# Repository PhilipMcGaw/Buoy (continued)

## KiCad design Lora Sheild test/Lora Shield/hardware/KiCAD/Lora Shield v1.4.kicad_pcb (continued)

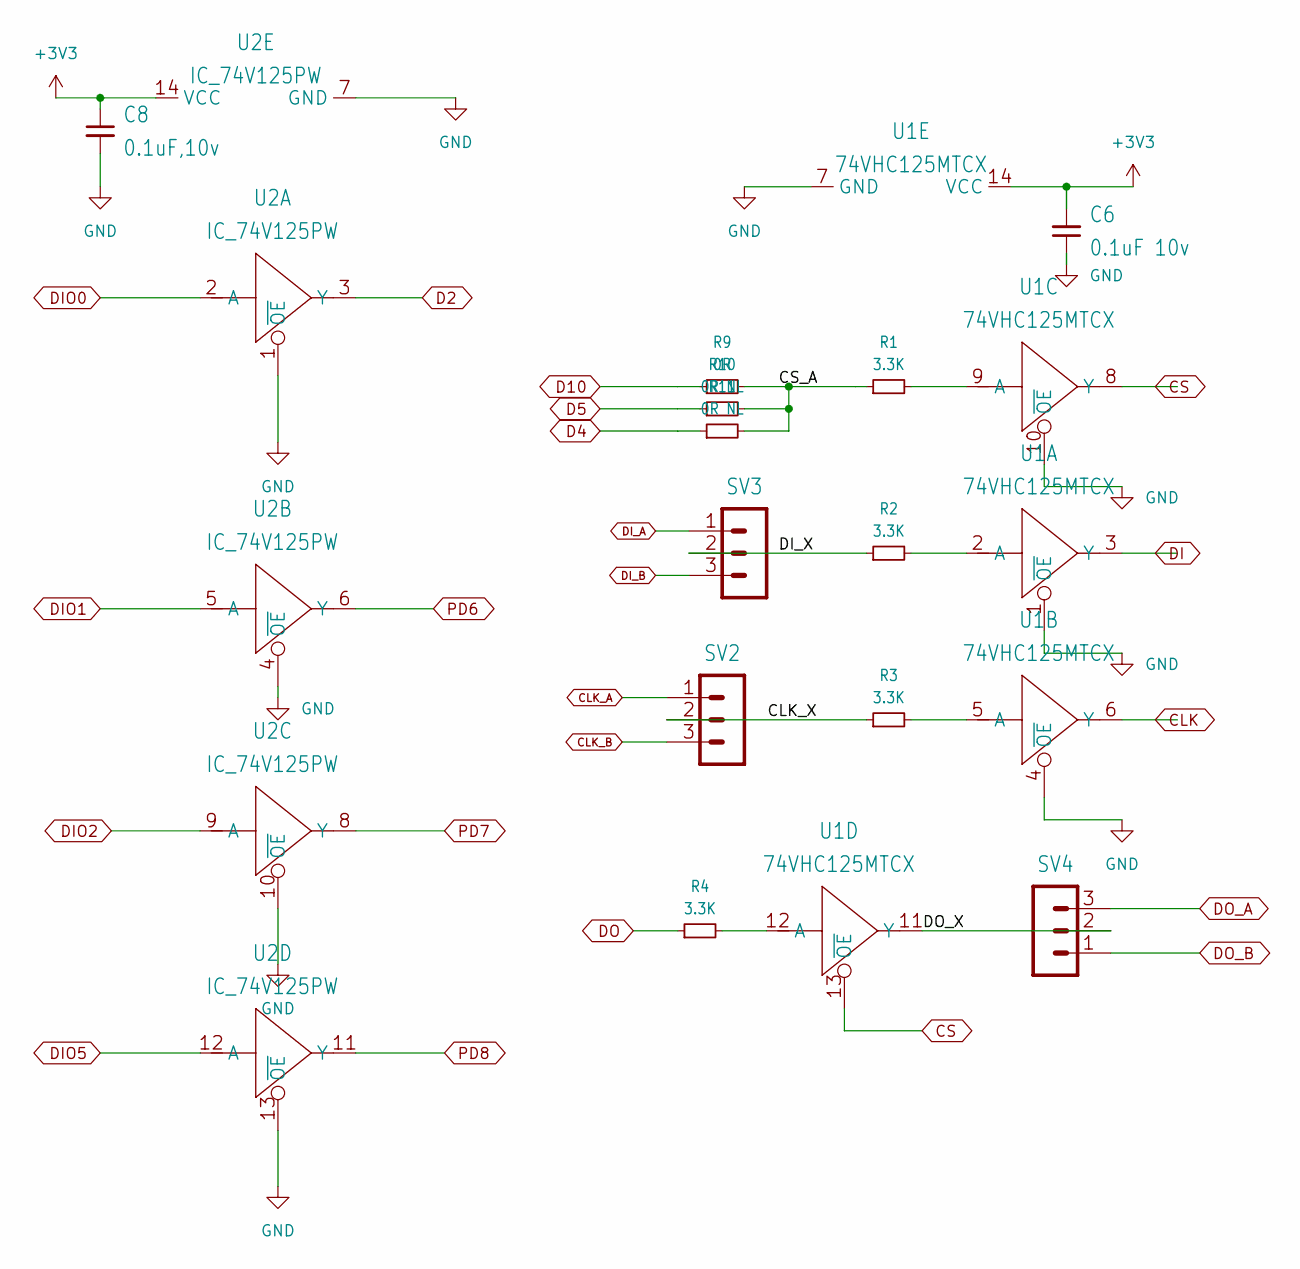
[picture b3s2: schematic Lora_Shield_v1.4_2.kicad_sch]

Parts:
C6: 0.1uF 10v; C0805
C8: 0.1uF,10v; C0805
R1, R2, R3, R4: 3.3K; R0603
R9: 0R; R0603
R10, R11: 0R NL; R0603
SV2, SV3, SV4: MA03-1
U1: 74VHC125MTCX; TSSOP14
U2: IC_74V125PW; IC_TSSOP14

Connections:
3V3: C6.2, C8.1, U1.14 (VCC), U2.14 (VCC); also elsewhere on the board
CLK: U1.6 (Y); also elsewhere on the board
CLK_A: SV2.1; also elsewhere on the board
CLK_B: SV2.3; also elsewhere on the board
CLK_X: R3.1, SV2.2
CS: U1.8 (Y), U1.13 (~OE); also elsewhere on the board
CS_A: R1.1, R9.2, R10.2, R11.2
D2: U2.3 (Y); also elsewhere on the board
D4: R11.1; also elsewhere on the board
D5: R10.1; also elsewhere on the board
D10: R9.1; also elsewhere on the board
DI: U1.3 (Y); also elsewhere on the board
DIO0: U2.2 (A); also elsewhere on the board
DIO1: U2.5 (A); also elsewhere on the board
DIO2: U2.9 (A); also elsewhere on the board
DIO5: U2.12 (A); also elsewhere on the board
DI_A: SV3.1; also elsewhere on the board
DI_B: SV3.3; also elsewhere on the board
DI_X: R2.1, SV3.2
DO: R4.1; also elsewhere on the board
DO_A: SV4.3; also elsewhere on the board
DO_B: SV4.1; also elsewhere on the board
DO_X: SV4.2, U1.11 (Y)
GND: C6.1, C8.2, U1.1 (~OE), U1.4 (~OE), U1.7 (GND), U1.10 (~OE), U2.1 (~OE), U2.4 (~OE), U2.7 (GND), U2.10 (~OE), U2.13 (~OE); also elsewhere on the board
unnamed: R4.2, U1.12 (A)
unnamed: R3.2, U1.5 (A)
unnamed: R2.2, U1.2 (A)
unnamed: R1.2, U1.9 (A)
PD6: U2.6 (Y); also elsewhere on the board
PD7: U2.8 (Y); also elsewhere on the board
PD8: U2.11 (Y); also elsewhere on the board

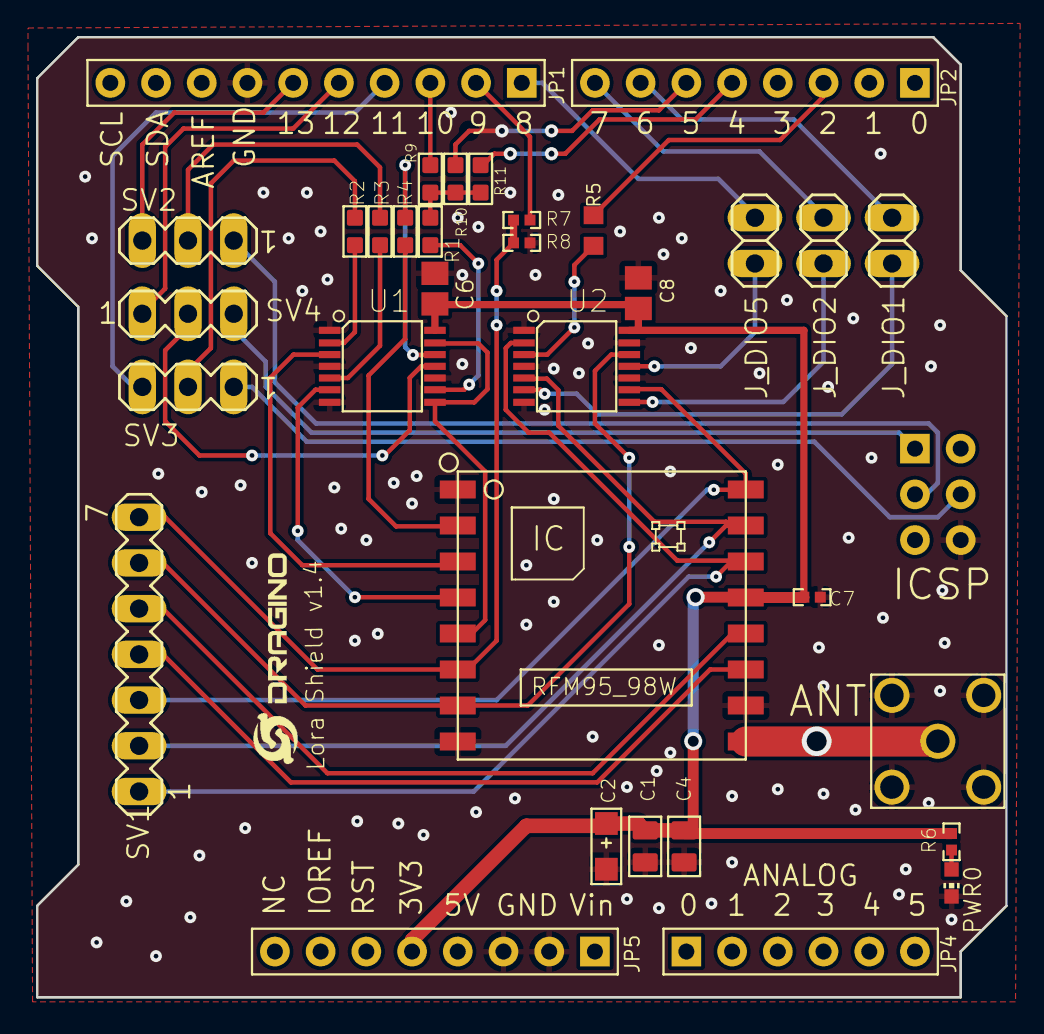
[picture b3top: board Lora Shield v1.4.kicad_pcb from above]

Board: 2 copper layers, 53.8 x 53.3 mm, 31 parts (0 on the bottom side), 41 nets.

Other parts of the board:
R5: 0; R0603
U$1: LOGO-NEW; LOGO-SILK-NEW

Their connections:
D2: R5.2; also elsewhere on the board
unnamed 30: R5.1; also elsewhere on the board

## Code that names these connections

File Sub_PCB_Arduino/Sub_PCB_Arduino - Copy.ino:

#include <Arduino.h>


// https://www.gammon.com.au/forum/?id=11428

#include "src/RS485_protocol/RS485_protocol.h"
#include <SoftwareSerial.h>

// Serial number etc
#include "ArduinoUniqueID.h"
#include "Adler16.h"

// These are required for the I2C 20x4 LCD screen used for diagnostics.
#include <LiquidCrystal_I2C.h>
#include <Wire.h>

// initialize the liquid crystal library
// the first parameter is  the I2C address
// the second parameter is how many rows are on your screen
// the  third parameter is how many columns are on your screen
LiquidCrystal_I2C lcd(0x27,  20, 4);

#define SERIAL_PORT_SPEED 9600
#define CompileDate __DATE__
#define CompileTime __TIME__

// Built in LED for heartbeat
const byte LED_PIN = 13;
bool LED_STATUS = true;
unsigned long previousMillis = 0;  // will store last time LED was updated
const uint8_t LED_Frequancy = 1;  // frequancy in Hz at which to blink
uint8_t heartBeatCNT = 0; // this will overflow at 255


// RS485 Pins
const byte UART1_TX = 2;
const byte UART1_TX_EN = 3;
const byte UART1_RX = 4;

// Address pins
const int ADDR_PIN_1 = A1;
const int ADDR_PIN_2 = A2;
uint8_t Address = 0;

const String softwareVersion = String(CompileDate) + " " + String(CompileTime); // Software version string
String serialNumber = "NAN";

String adler(String text)
{
  Adler16 adler16;
  adler16.begin();
  for (int j = 0; text[j] != 0; j++) {
    adler16.add(text[j]);
  }
  text = String(adler16.getAdler(), HEX);
  text.toUpperCase();
  return text;
}


SoftwareSerial rs485 (UART1_RX, UART1_TX);  // receive pin, transmit pin

int address(int pin_1 = 0, int pin_2 = 0, int pin_3 = 0)
{
  // Pin three is un-used at the moment.
  uint8_t Addr_1 = analogRead(pin_1);
  uint8_t Addr_2 = analogRead(pin_2);

//  Serial.println("--------");
//  Serial.print("raw: "); 
//  Serial.print(Addr_1);
//  Serial.print(" - ");
//  Serial.println(Addr_2);

  Addr_1 = map(Addr_1, 0, 255, 0, 2);
  Addr_2 = map(Addr_2, 0, 255, 0, 2);

//  Serial.print("map: ");
//  Serial.print(Addr_1);
//  Serial.print(" - ");
//  Serial.println(Addr_2);

  if (Addr_2 == 0) {
    Addr_2 = 0;
  } else if (Addr_2 == 1) {
    Addr_2 = 3;
  } else {
    Addr_2 = 6;
  }
  
  Address = Addr_1 + Addr_2;
  
//  Serial.print("val: ");
//  Serial.print(Addr_1);
//  Serial.print(" - ");
//  Serial.print(Addr_2);
//  Serial.print(" - ");
//  Serial.println(Address);

  return Address;
}

String SerialNumber ()
{
  String sn;
  for (size_t i = 0; i < UniqueIDsize; i++)
  {
    sn += String(UniqueID[i], HEX);
  }
  sn.toUpperCase();
  return sn;
}

// callback routines

void heartbeat()
{
    if (millis() - previousMillis >= ( 500 / LED_Frequancy)) {
    // 500 is half a second / frequancy in Hz.
    // save the last time you blinked the LED
    previousMillis = millis();
    
    // if the LED is off turn it on and vice-versa:
    if (LED_STATUS == true) {
      LED_STATUS = false;
    } else {
      LED_STATUS = true;
    }

    heartBeatCNT ++;  // increase the counter at twice the LED frequancy

    digitalWrite(LED_PIN,LED_STATUS); // Set the LED status
  }
}
  
void fWrite (const byte what)
{
  rs485.write (what);  
}
  
int fAvailable ()
{
  return rs485.available ();  
}

int fRead ()
{
  return rs485.read ();  
}

void setup()
{
  rs485.begin (SERIAL_PORT_SPEED);
  Serial.begin (SERIAL_PORT_SPEED);
  pinMode (UART1_TX_EN, OUTPUT);    // RS485 driver output enable
  pinMode (LED_PIN, OUTPUT);        // built-in LED Pin
  digitalWrite(LED_PIN,LED_STATUS); // Turn the built-in LED on

  lcd.init(); //initialize lcd screen
  lcd.clear(); // Clears the LCD screen 

  lcd.backlight(); // turn on the backlight

  Address = address(ADDR_PIN_1, ADDR_PIN_2); // Read in the value from the two address pins
  serialNumber = SerialNumber(); // Gets the raw string
  serialNumber = adler(serialNumber); // Gets the adled verion
}


void loop()
{
  heartbeat();

  lcd.setCursor(0,0);
  lcd.print("Sub PCB Diagnostics");
  lcd.setCursor(0,1);
  lcd.print("ADDR: " + String(Address));
  lcd.setCursor(9,1);
  lcd.print("SN: " + String(serialNumber));
  lcd.setCursor(0,3);
  lcd.print("Heartbeat:      "); 
  lcd.setCursor(0,3);
  lcd.print("Heartbeat: " + String(heartBeatCNT)); 

}  // end of loop

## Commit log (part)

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2025-07-28 Added KiCAD PCB start
2025-07-28 Blank 100 x 100 PCB
    this will need cleaned up if it continues to be used.
2025-07-28 PCB sub assembly
2025-07-28 battery charging
2025-07-28 Add Assets
2025-07-28 updated 18650
2025-07-29 Added STLs
2025-08-12 this is likely to break all the things…
2025-08-15 updated assets
2025-08-15 clean
2025-08-15 moved connector
2025-08-18 Update .wget-hsts
2025-08-18 remove dupes
2025-08-18 moved files
2025-08-18 auto save del
2025-08-21 libery change
2025-09-02 Now uses the ones in template folder
2025-09-02 removed shrimp and replaced with Arduino Mega 328
2025-09-04 Changed Micro
2025-09-04 imported from https://github.com/dragino/Lora/tree/master/Lora%20Shield/hardware/v1.4
    https://github.com/dragino/Lora/tree/master/Lora%20Shield/hardware/v1.4
2025-09-04 Convert to KiCad
2025-09-05 LoRa
2025-09-12 cleanup
2025-09-12 HT Wireless Tracker added
2025-09-12 File name update
2025-09-13 changes adn updates
2026-05-03 known good
2026-06-11 edited git ignore and git attributes
